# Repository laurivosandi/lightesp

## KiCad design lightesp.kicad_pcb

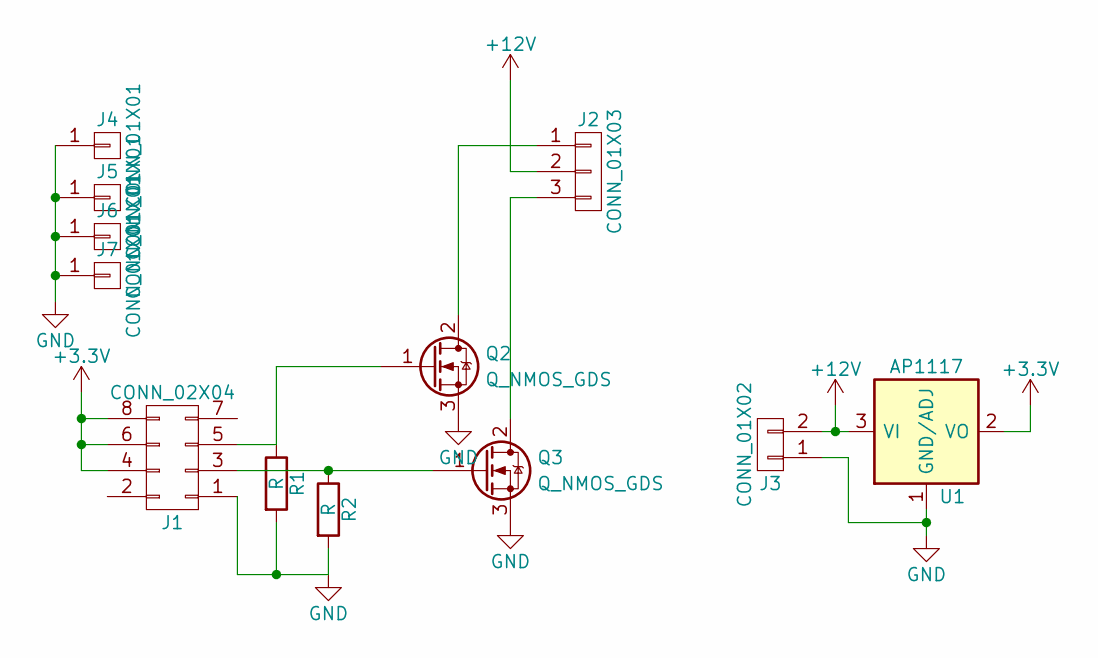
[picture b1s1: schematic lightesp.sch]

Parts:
J1: CONN_02X04; Socket_Strip_Straight_2x04_Pitch2.54mm
J2: CONN_01X03; TerminalBlock_Pheonix_PT-3.5mm_3pol
J3: CONN_01X02; TerminalBlock_Pheonix_PT-3.5mm_2pol
J4, J5, J6, J7: CONN_01X01; 1pin
Q2, Q3: Q_NMOS_GDS; TO-220_Vertical
R1, R2: R; R_Axial_DIN0204_L3.6mm_D1.6mm_P7.62mm_Horizontal
U1: AP1117; SOT-223

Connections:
+3V3: J1.4, J1.6, J1.8, U1.2 (VO), U1.4 (VO)
+12V: J2.2, J3.2, U1.3 (VI)
GND: J1.1, J3.1, J4.1, J5.1, J6.1, J7.1, Q2.3 (S), Q3.3 (S), R1.2, R2.2, U1.1 (GND/ADJ)
unnamed: J1.3, Q3.1 (G), R2.1
unnamed: J1.5, Q2.1 (G), R1.1
unnamed: J2.1, Q2.2 (D)
unnamed: J2.3, Q3.2 (D)

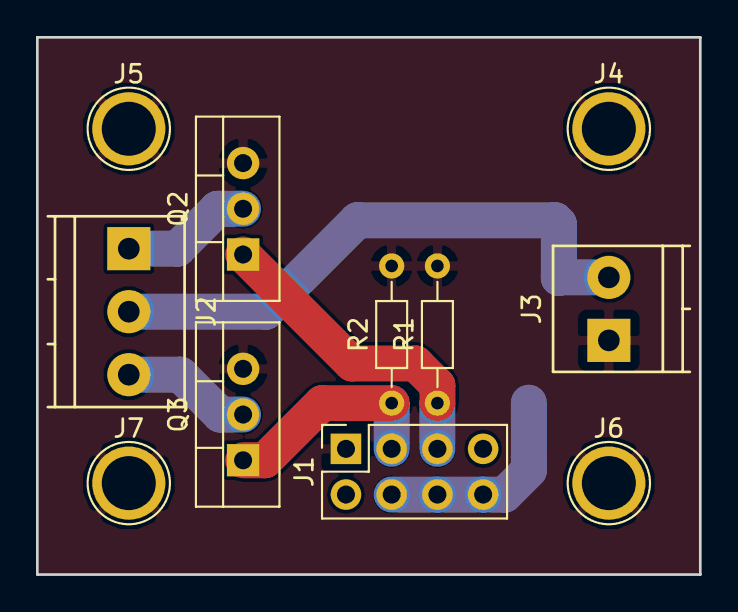
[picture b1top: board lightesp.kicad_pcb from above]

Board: 2 copper layers, 36.8 x 29.8 mm, 12 parts (1 on the bottom side), 7 nets.
